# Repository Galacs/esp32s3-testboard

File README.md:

# esp32s3-testboard
ESP32-S3 dev/poc board with some sensors

This is the first pcb with a microcontroller that I designed. It works with ESP32-S3-WROOM modules.

List of IC used on the board:
- ESP32-S3-WROOM-1 (Main MCU)
- BMP280 (i2C/SPI pressure and temperature sensor)
- CP2102N (USB-to-UART)
- SK6812 (RGBW led)
- LIS2DW12 (3-axis accelerometer)

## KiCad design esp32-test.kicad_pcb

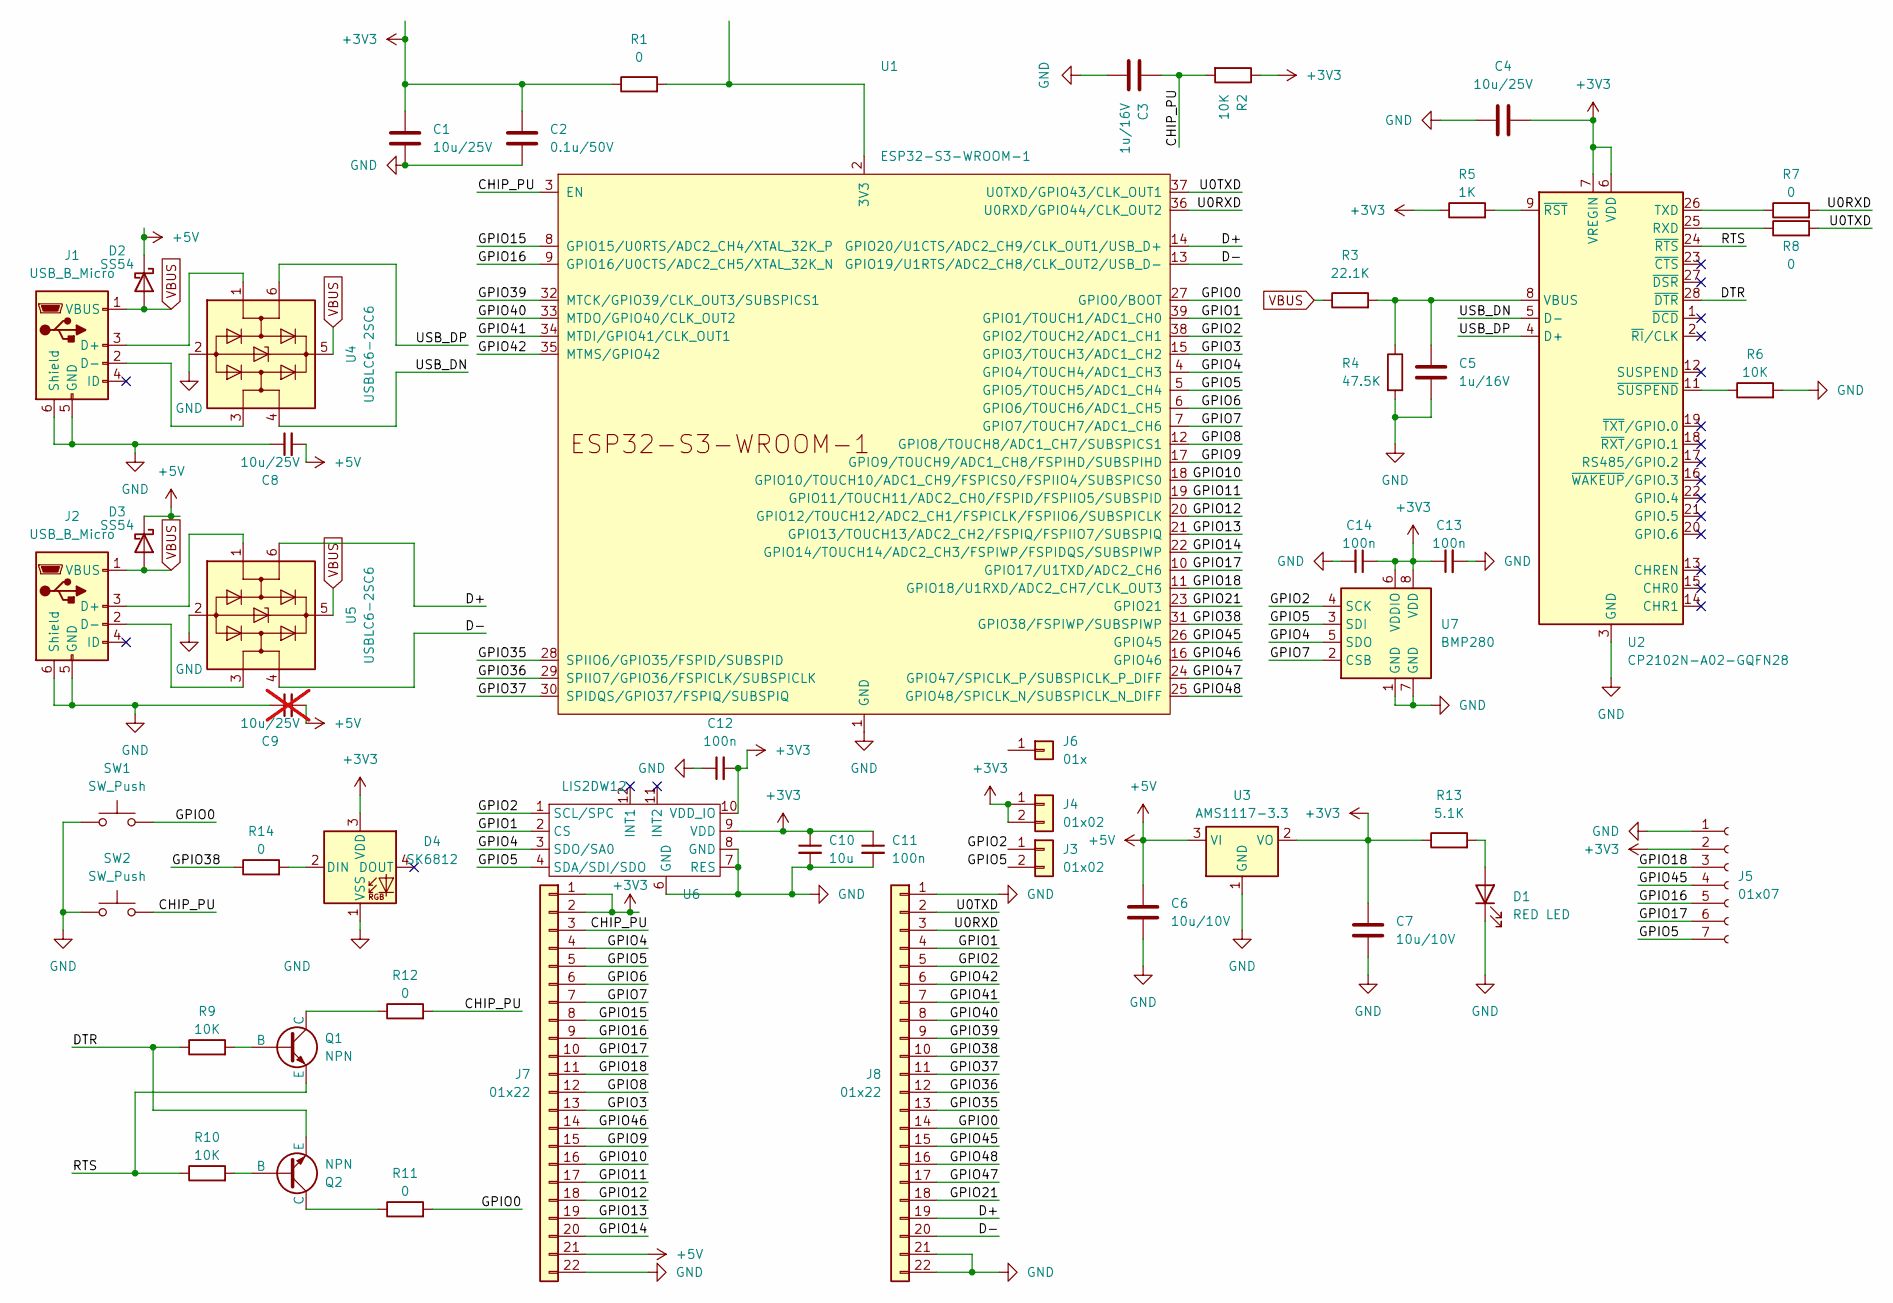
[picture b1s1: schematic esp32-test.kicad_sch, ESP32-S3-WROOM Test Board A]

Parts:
C1, C4, C8: 10u/25V; C_0603_1608Metric
C2: 0.1u/50V; C_0402_1005Metric
C3, C5: 1u/16V; C_0603_1608Metric
C6, C7: 10u/10V; C_0603_1608Metric
C9: 10u/25V; C_0603_1608Metric; not fitted
C10: 10u; C_0603_1608Metric
C11, C12, C13, C14: 100n; C_0402_1005Metric_Pad0.74x0.62mm_HandSolder
D1: RED LED; LED_0805_2012Metric
D2, D3: SS54; D_SMA
D4: SK6812; LED_SK6812_PLCC4_5.0x5.0mm_P3.2mm
J1, J2: USB_B_Micro; USB_Micro-B_XKB_U254-051T-4BH83-F1S
J3, J4: 01x02; PinHeader_1x02_P2.54mm_Vertical
J5: 01x07; PinSocket_1x07_P2.54mm_Vertical
J6: 01x; PinSocket_1x01_P2.54mm_Vertical
J7, J8: 01x22; PinHeader_1x22_P2.54mm_Vertical
Q1, Q2: NPN; SOT-23
R1, R7, R8, R11, R12, R14: 0; R_0603_1608Metric
R2, R6, R9, R10: 10K; R_0603_1608Metric
R3: 22.1K; R_0805_2012Metric
R4: 47.5K; R_0603_1608Metric
R5: 1K; R_0603_1608Metric
R13: 5.1K; R_0603_1608Metric
SW1, SW2: SW_Push; SW_Push_1P1T_XKB_TS-1187A
U1: ESP32-S3-WROOM-1
U2: CP2102N-A02-GQFN28; QFN-28-1EP_5x5mm_P0.5mm_EP3.35x3.35mm
U3: AMS1117-3.3; SOT-223-3_TabPin2
U4, U5: USBLC6-2SC6; SOT-23-6
U6: LIS2DW12; LGA-12_2x2mm_P0.5mm
U7: BMP280; Bosch_LGA-8_2x2.5mm_P0.65mm_ClockwisePinNumbering

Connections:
+3V3: C1.1, C2.1, C4.2, C7.1, C10.1, C11.1, C12.2, C13.1, C14.1, D4.3 (VDD), J4.1, J4.2, J5.2, J7.1, J7.2, R1.1, R2.1, R5.1, R13.1, U2.6 (VDD), U2.7 (VREGIN), U3.2 (VO), U6.9 (VDD), U6.10 (VDD_IO), U7.6 (VDDIO), U7.8 (VDD)
+5V: C6.1, C8.2, C9.2, D2.1 (K), D3.1 (K), J7.21, U3.3 (VI)
/CHIP_PU: C3.1, J7.3, R2.2, R12.2, SW2.2, U1.3 (EN)
/D+: J8.19, U1.14 (GPIO20/U1CTS/ADC2_CH9/CLK_OUT1/USB_D+), U5.6 (I/O1)
/D-: J8.20, U1.13 (GPIO19/U1RTS/ADC2_CH8/CLK_OUT2/USB_D-), U5.4 (I/O2)
/DTR: Q2.3 (E), R9.1, U2.28 (~DTR)
/GPIO0: J8.14, R11.2, SW1.2, U1.27 (GPIO0/BOOT)
/GPIO1: J8.4, U1.39 (GPIO1/TOUCH1/ADC1_CH0), U6.2 (CS)
/GPIO2: J3.1, J8.5, U1.38 (GPIO2/TOUCH2/ADC1_CH1), U6.1 (SCL/SPC), U7.4 (SCK)
/GPIO3: J7.13, U1.15 (GPIO3/TOUCH3/ADC1_CH2)
/GPIO4: J7.4, U1.4 (GPIO4/TOUCH4/ADC1_CH3), U6.3 (SDO/SA0), U7.5 (SDO)
/GPIO5: J3.2, J5.7, J7.5, U1.5 (GPIO5/TOUCH5/ADC1_CH4), U6.4 (SDA/SDI/SDO), U7.3 (SDI)
/GPIO6: J7.6, U1.6 (GPIO6/TOUCH6/ADC1_CH5)
/GPIO7: J7.7, U1.7 (GPIO7/TOUCH7/ADC1_CH6), U7.2 (CSB)
/GPIO8: J7.12, U1.12 (GPIO8/TOUCH8/ADC1_CH7/SUBSPICS1)
/GPIO9: J7.15, U1.17 (GPIO9/TOUCH9/ADC1_CH8/FSPIHD/SUBSPIHD)
/GPIO10: J7.16, U1.18 (GPIO10/TOUCH10/ADC1_CH9/FSPICS0/FSPIIO4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)
/GPIO11: J7.17, U1.19 (GPIO11/TOUCH11/ADC2_CH0/FSPID/FSPIIO5/S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)
/GPIO12: J7.18, U1.20 (GPIO12/TOUCH12/ADC2_CH1/FSPICLK/FSPIIO6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)
/GPIO13: J7.19, U1.21 (GPIO13/TOUCH13/ADC2_CH2/FSPIQ/FSPIIO7/S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)
/GPIO14: J7.20, U1.22 (GPIO14/TOUCH14/ADC2_CH3/FSPIWP/FSPIDQS/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)
/GPIO15: J7.8, U1.8 (GPIO15/U0RTS/ADC2_CH4/XTAL_32K_P)
/GPIO16: J5.5, J7.9, U1.9 (GPIO16/U0CTS/ADC2_CH5/XTAL_32K_N)
/GPIO17: J5.6, J7.10, U1.10 (GPIO17/U1TXD/ADC2_CH6)
/GPIO18: J5.3, J7.11, U1.11 (GPIO18/U1RXD/ADC2_CH7/CLK_OUT3)
/GPIO21: J8.18, U1.23 (GPIO21)
/GPIO35: J8.13, U1.28 (SPIIO6/GPIO35/FSPID/SUBSPID)
/GPIO36: J8.12, U1.29 (SPIIO7/GPIO36/FSPICLK/SUBSPICLK)
/GPIO37: J8.11, U1.30 (SPIDQS/GPIO37/FSPIQ/SUBSPIQ)
/GPIO38: J8.10, R14.1, U1.31 (GPIO38/FSPIWP/SUBSPIWP)
/GPIO39: J8.9, U1.32 (MTCK/GPIO39/CLK_OUT3/SUBSPICS1)
/GPIO40: J8.8, U1.33 (MTDO/GPIO40/CLK_OUT2)
/GPIO41: J8.7, U1.34 (MTDI/GPIO41/CLK_OUT1)
/GPIO42: J8.6, U1.35 (MTMS/GPIO42)
/GPIO45: J5.4, J8.15, U1.26 (GPIO45)
/GPIO46: J7.14, U1.16 (GPIO46)
/GPIO47: J8.17, U1.24 (GPIO47/SPICLK_P/SUBSPICLK_P_DIFF)
/GPIO48: J8.16, U1.25 (GPIO48/SPICLK_N/SUBSPICLK_N_DIFF)
/RTS: Q1.3 (E), R10.1, U2.24 (~RTS)
/U0RXD: J8.3, R7.2, U1.36 (U0RXD/GPIO44/CLK_OUT2)
/U0TXD: J8.2, R8.2, U1.37 (U0TXD/GPIO43/CLK_OUT1)
/USB_DN: U2.5 (D-), U4.4 (I/O2)
/USB_DP: U2.4 (D+), U4.6 (I/O1)
GND: C1.2, C2.2, C3.2, C4.1, C5.2, C6.2, C7.2, C8.1, C9.1, C10.2, C11.2, C12.1, C13.2, C14.2, D1.1 (K), D4.1 (VSS), J1.5 (GND), J1.6 (Shield), J2.5 (GND), J2.6 (Shield), J5.1, J7.22, J8.1, J8.21, J8.22, R4.2, R6.2, SW1.1, SW2.1, U1.1 (GND), U1.40 (GND), U1.41 (GND), U2.3 (GND), U2.29 (GND), U3.1 (GND), U4.2 (GND), U5.2 (GND), U6.6 (GND), U6.7 (RES), U6.8 (GND), U7.1 (GND), U7.7 (GND)
unnamed: D1.2 (A), R13.2
unnamed: D4.2 (DIN), R14.2
unnamed: J1.3 (D+), U4.1 (I/O1)
unnamed: J1.2 (D-), U4.3 (I/O2)
unnamed: J2.3 (D+), U5.1 (I/O1)
unnamed: J2.2 (D-), U5.3 (I/O2)
unnamed: Q1.2 (B), R9.2
unnamed: Q1.1 (C), R12.1
unnamed: Q2.2 (B), R10.2
unnamed: Q2.1 (C), R11.1
unnamed: R1.2, U1.2 (3V3)
unnamed: R8.1, U2.25 (RXD)
unnamed: R7.1, U2.26 (TXD)
unnamed: C5.1, R3.2, R4.1, U2.8 (VBUS)
unnamed: R5.2, U2.9 (~RST)
unnamed: R6.1, U2.11 (~SUSPEND)
VBUS: D2.2 (A), D3.2 (A), J1.1 (VBUS), J2.1 (VBUS), R3.1, U4.5 (VBUS), U5.5 (VBUS)

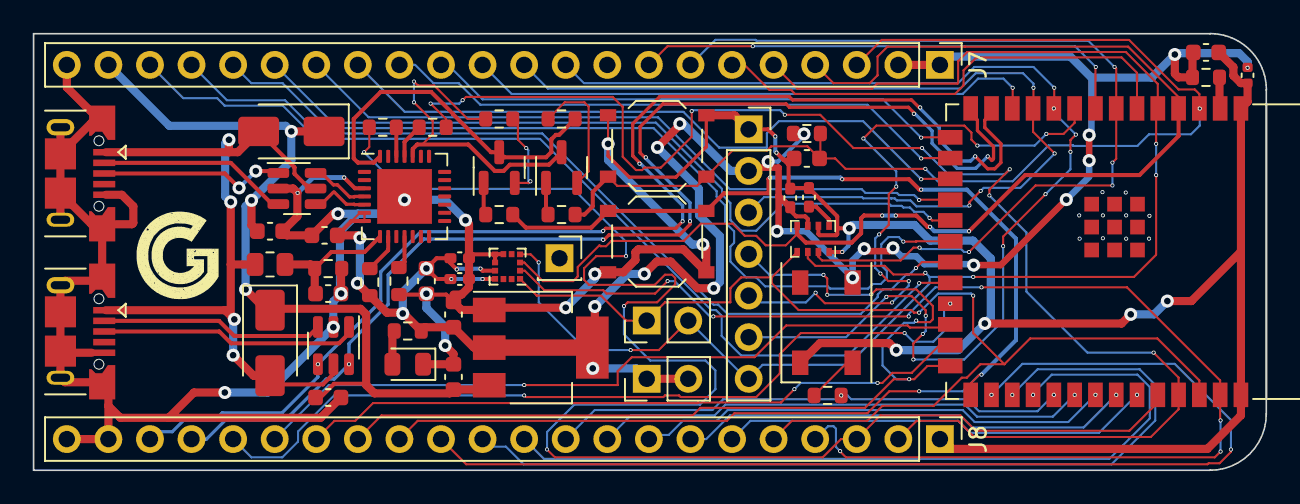
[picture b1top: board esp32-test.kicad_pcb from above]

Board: 2 copper layers, 75.3 x 26.7 mm, 51 parts (0 on the bottom side), 61 nets.

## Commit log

2023-09-23 added README file
